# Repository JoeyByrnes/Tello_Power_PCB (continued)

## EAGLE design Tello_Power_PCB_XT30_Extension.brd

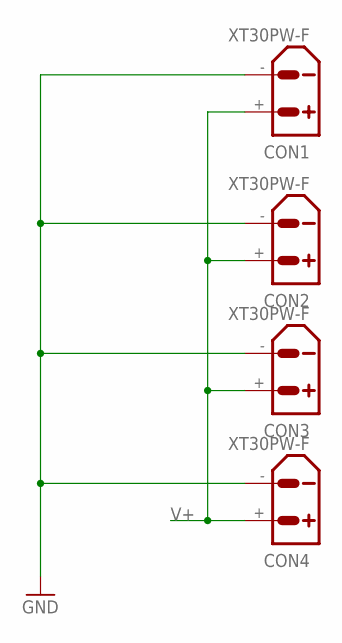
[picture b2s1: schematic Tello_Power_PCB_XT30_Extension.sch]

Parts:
CON1, CON2, CON3, CON4: XT30PW-F

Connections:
GND: CON1.-, CON2.-, CON3.-, CON4.-
V+: CON1.+, CON2.+, CON3.+, CON4.+

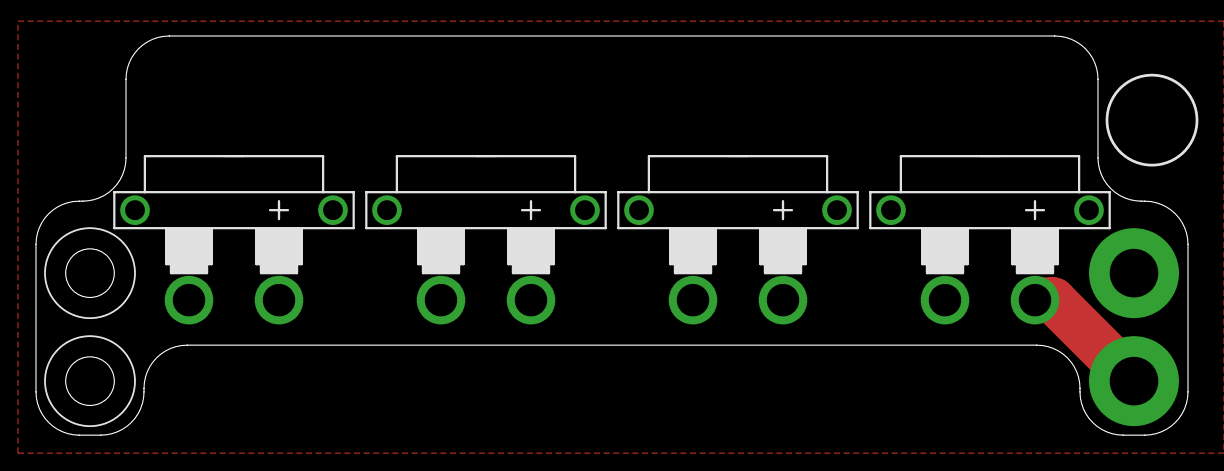
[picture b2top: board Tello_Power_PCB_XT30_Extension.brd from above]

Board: 2 copper layers, 64.0 x 22.2 mm, 4 parts (0 on the bottom side), 2 nets.

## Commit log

2022-09-12 Started laying out PCB
2022-09-16 Most things laid out
2022-09-16 added XT30 Expansion PCB
2022-09-19 Added motor PMOS stage
2022-09-19 Routed about half of pcb
2022-09-22 Made big changes to power distr.
2022-09-23 added ADC and 5V-AO
2022-09-23 Finished Routing PCB, Needs Design Review
2022-09-23 updated readme-visuals
2022-09-24 added UV 30s delay circuit
2022-09-27 Organized Schematic, Ready for Detailed Review
2022-09-27 Increased internal GND conn. widths
2022-09-27 Organized Schematic
2022-09-27 Review Finished
2022-09-28 Added mfg files and renders
2022-09-28 added 3d model
2023-10-02 updated readme photos
2023-10-18 updated high side switch resistors
